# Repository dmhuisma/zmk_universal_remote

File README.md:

# ZMK Universal Remote

A simple remote for a living-room HTPC. Off-the-shelf remotes tend to feel cheap and lack the simple navigation people now expect from a streaming box. This remote has only the basic buttons a streaming box remote has: a D-pad, back, home and media controls. A touchscreen adds Home Assistant controls and a touchpad.

This repository contains the PCB, the 3D-printable case and the [ZMK](https://zmk.dev/) firmware.

> **Note:** This remote needs a second revision to solve connectivity issues. The antenna is placed under where you grip with your hand, which blocks the signal. The rev 2 design is currently in progress, so different parts of the design (board, firmware, case) may not match up in current state.

## Features

- **Streaming-box button layout:** a 5-way D-pad plus six buttons for navigation and media. There are no rows of rarely used buttons.
- **Quiet, soft-feeling buttons:** the remote uses Alps **SKPMAME010** tactile switches, which give soft tactile feedback instead of the loud clicks of cheaper remotes.
- **Touchscreen:** a 1.9" 170×320 capacitive touch LCD (Waveshare, ST7789V2 / CST816S) with a tabbed UI built with LVGL.
- **Home Assistant control over BTHome:** touchscreen buttons send BTHome Bluetooth advertisements, which nearby ESPHome Bluetooth proxies pick up. Taps and long presses are separate events.
- **Touchpad and air mouse:** the Touchpad screen controls the PC's mouse pointer. On that screen, tilting the remote also moves the pointer, using the accelerometer.
- **USB dongle connection:** a USB dongle plugged into the PC connects to the remote quickly and easily. *(Planned; not set up yet.)*
- **Infrared TX and RX:** two IR LEDs (wide and narrow beam) control TVs and other devices that aren't part of the smart home. A TSOP38238 receiver can learn codes from existing remotes.
- **Wake on motion:** an MPU6050 accelerometer wakes the remote from deep sleep when you pick it up, so you don't need to press a button first.
- **Display backlight:** adjustable brightness, and the backlight turns off when the remote is idle.
- **Rechargeable battery:** the case has room for a flat LiPo of about 1000 mAh (not verified yet). It charges over USB-C.
- **Sleep current:** 100 uA, with accelerometer motion wake enabled.
- **Active current:** >= 20 mA, depending on screen brightness
- **nice!nano (nRF52840) controller:** standard ZMK hardware with Bluetooth LE.

> **Note:** The touchscreen UI and its Home Assistant controls (scenes, lights, climate, vacuums) are built for my own home. If you build this remote, expect to customize the screens and automations for your setup. The physical buttons are general-purpose.

## Touchscreen interface

| Home: scenes | TV | TV › Mouse: touchpad |
|:---:|:---:|:---:|
|  |  |  |

## Repository layout

| Path | Contents |
|---|---|
| [`board/`](board/) | KiCad schematic and PCB |
| [`case/`](case/) | 3D-printable case (SolidCraft model and 3MF exports) |
| [`firmware/`](firmware/) | ZMK shield, custom drivers and Home Assistant tooling |

## Hardware

The PCB is a KiCad project. Main parts:

- nice!nano (nRF52840)
- 11 × Alps SKPMAME010 tactile switches in a diode matrix
- Waveshare 1.9" touch LCD (on a header)
- GY-521 MPU6050 accelerometer module (on a header)
- 2 × 5 mm IR LEDs driven by Si2302 MOSFETs, and a TSOP38238 IR receiver
- Flat LiPo battery, soldered directly to the nice!nano battery pads

> **Important:** Before you fit the GY-521 accelerometer module, desolder its power LED and its I2C pull-up resistors. The module stays powered during sleep, and with these parts left on, the sleep current is too high.

## Case

The case is modeled in SolidCraft ([`case/universal_remote_case.sc`](case/universal_remote_case.sc)). It is a two-part snap-fit shell with separate printed button caps, D-pad segments and an IR-transparent front window.

## Firmware

The firmware is a ZMK shield (`universal_remote`) for the `nice_nano//zmk` board. It also uses these modules:

- [zephyr-dt-lvgl](https://github.com/dmhuisma/zephyr-dt-lvgl): touchscreen UI defined in devicetree
- [zmk-ir](https://github.com/tadakado/zmk-ir): IR transmit and receive

The custom code in `firmware/src/` covers BTHome broadcasts, the touchpad, the motion pointer, wake-on-motion sleep and display brightness.

Build targets are listed in [`firmware/build.yaml`](firmware/build.yaml). This includes the `universal_remote_dongle` shield for an nRF52840 USB dongle. The local build and flash commands are in [`firmware/.vscode/tasks.json`](firmware/.vscode/tasks.json).

### Home Assistant

[`firmware/home_assistant/bthome_buttons.yaml`](firmware/home_assistant/bthome_buttons.yaml) lists every button the remote sends and the BTHome event each one fires. To generate a starter automation to edit:

```sh
cd firmware
uv run tools/gen_hass_automation.py home_assistant/bthome_buttons.yaml --address XX:XX:XX:XX:XX:XX
```

To watch the remote's advertisements live while you debug, use `tools/bthome_monitor.py`.

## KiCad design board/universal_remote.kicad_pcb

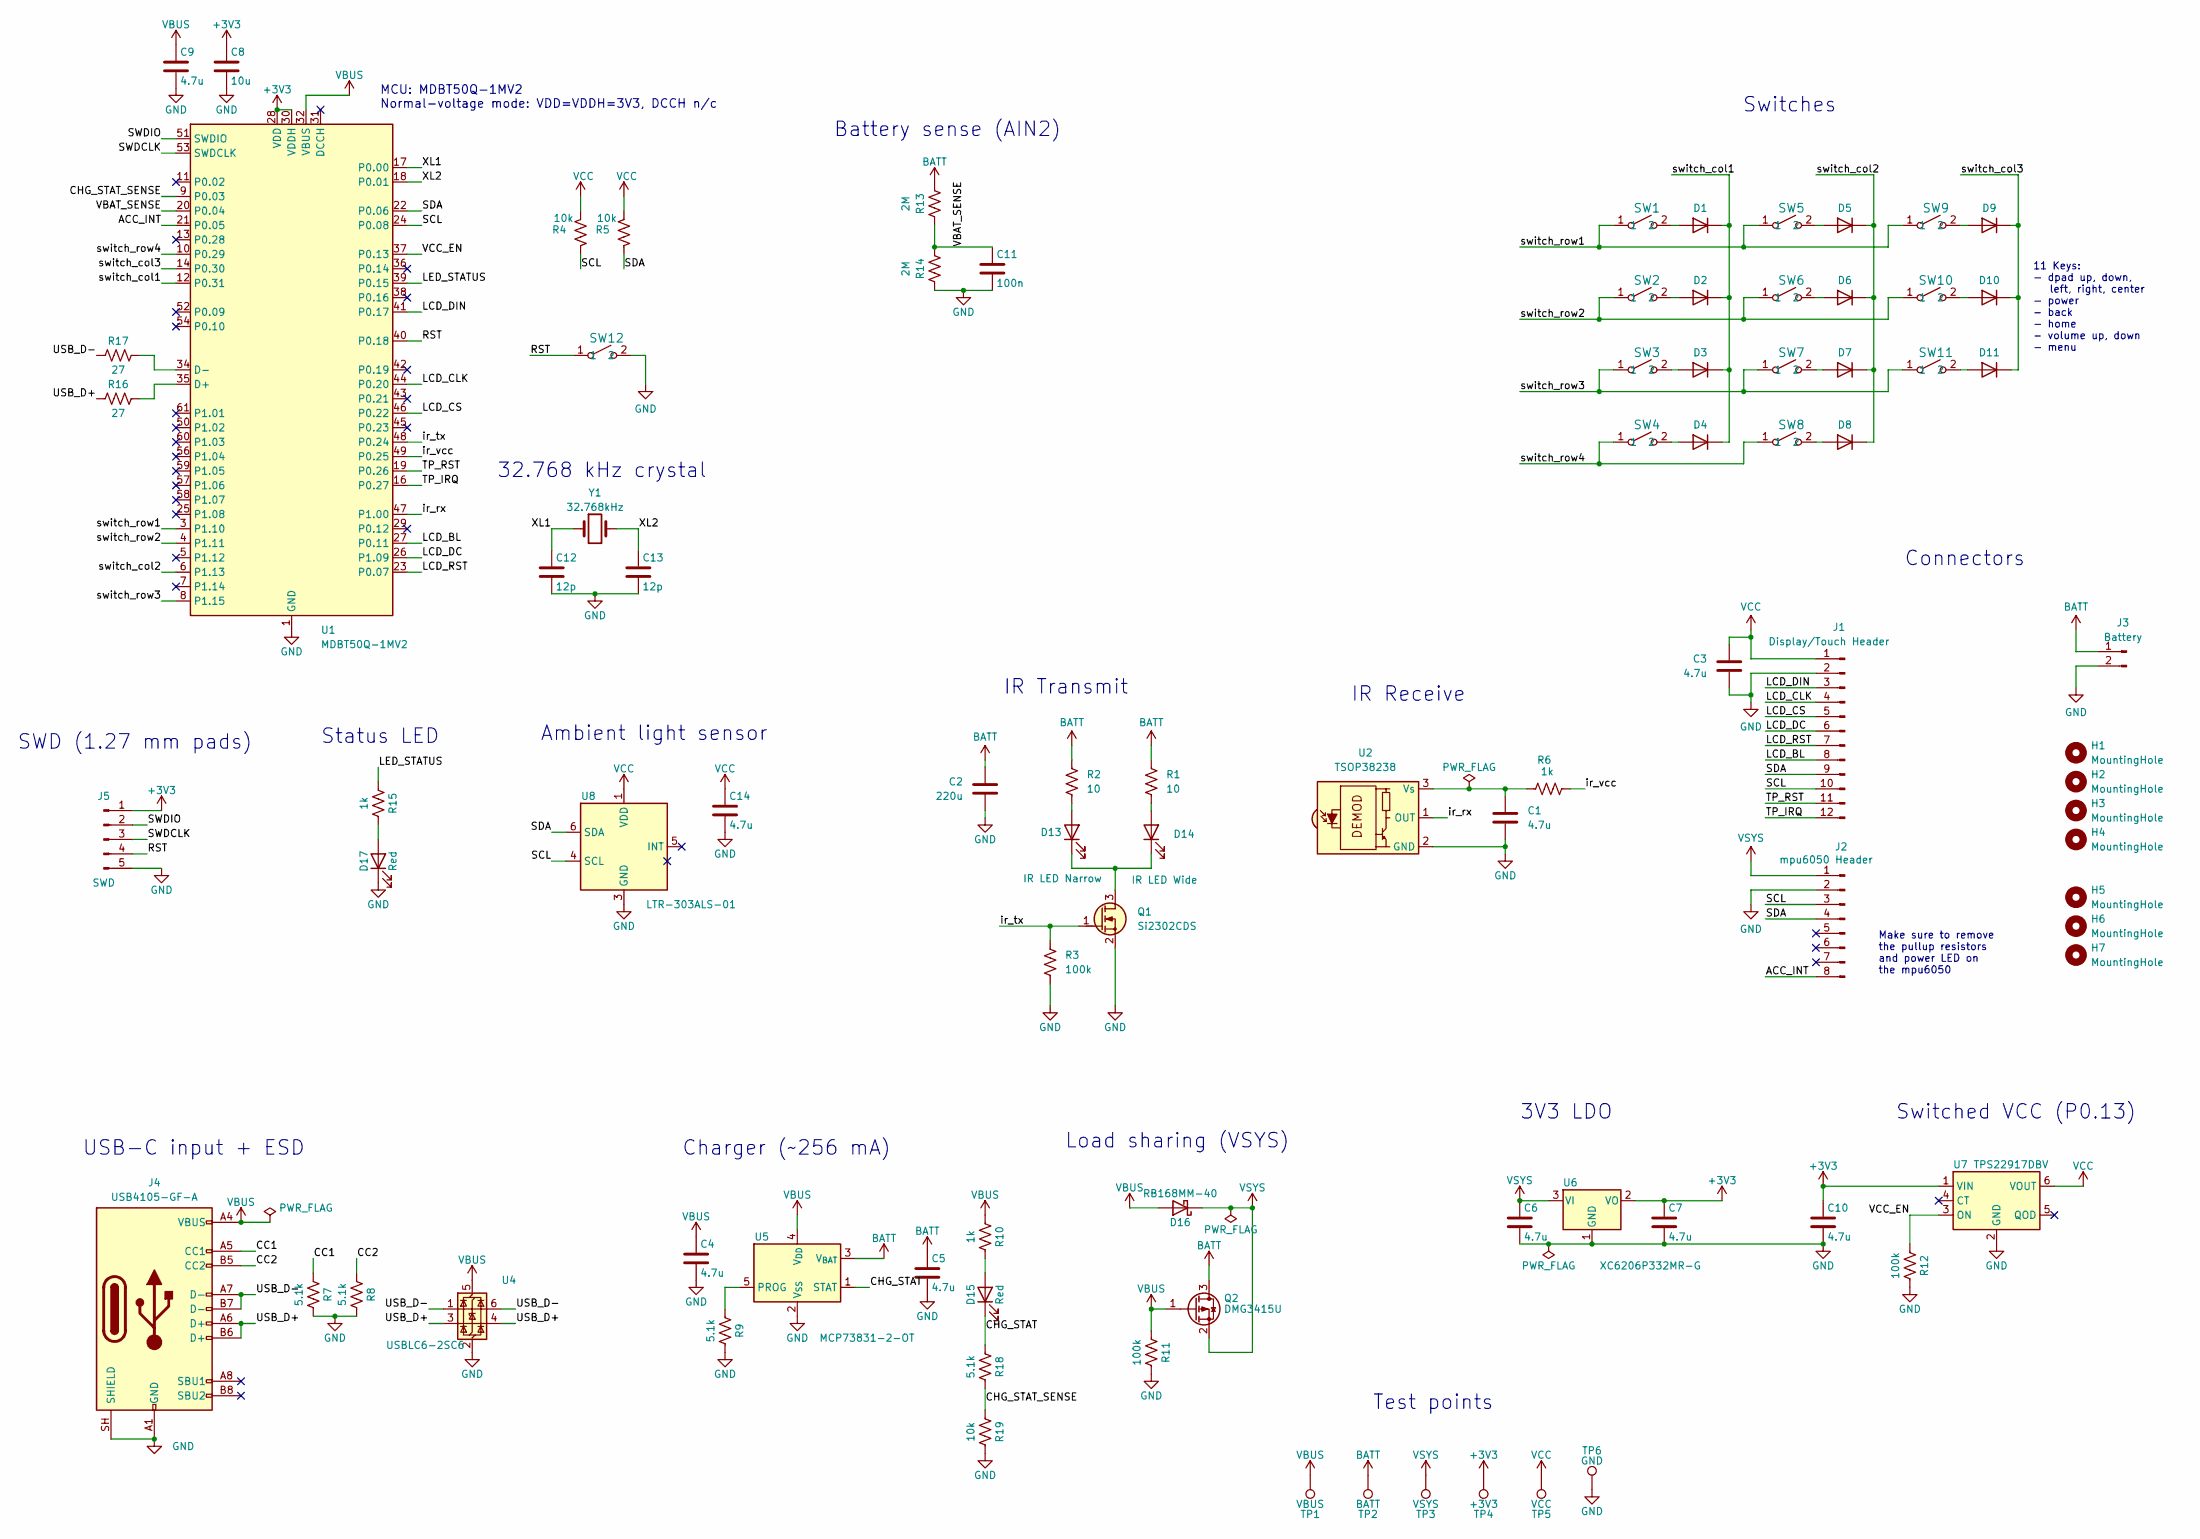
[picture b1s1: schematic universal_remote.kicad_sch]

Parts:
C1, C3, C4, C5, C6, C7, C9, C10, C14: 4.7u; C_0603_1608Metric_Pad1.08x0.95mm_HandSolder
C2: 220u; C_1210_3225Metric_Pad1.33x2.70mm_HandSolder
C8: 10u; C_0805_2012Metric_Pad1.18x1.45mm_HandSolder
C11: 100n; C_0603_1608Metric_Pad1.08x0.95mm_HandSolder
C12, C13: 12p; C_0603_1608Metric_Pad1.08x0.95mm_HandSolder
D1, D2, D3, D4, D5, D6, D7, D8, D9, D10, D11: D; D_DO-35_SOD27_P10.16mm_Horizontal
D13: IR LED Narrow; LED_D3.0mm; MPN Inolux INL-3AHIR15 (alt: INL-3AHIR30)
D14: IR LED Wide; LED_D3.0mm; MPN Everlight IR204/H16/L10 (DigiKey 1080-1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
D15, D17: Red; LED_0603_1608Metric_Pad1.05x0.95mm_HandSolder
D16: RB168MM-40; D_SOD-123F; MPN Rohm RB168MM-40TR (ultra-low IR, <=0.55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
H1, H2, H3, H4: MountingHole; MountingHole_2.2mm_M2
H5, H6, H7: MountingHole; MountingHole_3.2mm_M3
J1: Display/Touch Header; PinHeader_1x12_P2.54mm_Vertical
J2: mpu6050 Header; PinHeader_1x08_P2.54mm_Vertical
J3: Battery; PinHeader_1x02_P2.54mm_Vertical
J4: USB4105-GF-A; USB_C_Receptacle_GCT_USB4105-xx-A_16P_TopMnt_Horizontal; MPN GCT USB4105-GF-A
J5: SWD; PinHeader_1x05_P2.54mm_Vertical
Q1: Si2302CDS; SOT-23
Q2: DMG3415U; SOT-23; MPN DMG3415U-7
R1, R2: 10; R_1206_3216Metric_Pad1.30x1.75mm_HandSolder
R3, R11, R12: 100k; R_0603_1608Metric_Pad0.98x0.95mm_HandSolder
R4, R5, R19: 10k; R_0603_1608Metric_Pad0.98x0.95mm_HandSolder
R6, R10, R15: 1k; R_0603_1608Metric_Pad0.98x0.95mm_HandSolder
R7, R8, R9, R18: 5.1k; R_0603_1608Metric_Pad0.98x0.95mm_HandSolder
R13, R14: 2M; R_0603_1608Metric_Pad0.98x0.95mm_HandSolder
R16, R17: 27; R_0603_1608Metric_Pad0.98x0.95mm_HandSolder
SW1, SW2, SW3, SW4, SW5, SW6, SW7, SW8, SW9, SW10, SW11, SW12: SKPMAME010; SKPMAME010_ALPS
TP1: VBUS; TestPoint_Pad_D1.5mm
TP2: BATT; TestPoint_Pad_D1.5mm
TP3: VSYS; TestPoint_Pad_D1.5mm
TP4: +3V3; TestPoint_Pad_D1.5mm
TP5: VCC; TestPoint_Pad_D1.5mm
TP6: GND; TestPoint_Pad_D1.5mm
U1: MDBT50Q-1MV2; Raytac_MDBT50Q
U2: TSOP38238; Vishay_MINICAST-3Pin
U4: USBLC6-2SC6; SOT-23-6
U5: MCP73831-2-OT; SOT-23-5; MPN MCP73831T-2ACI/OT
U6: XC6206P332MR-G; SOT-23; MPN Torex XC6206P332MR-G (not the UMW XC620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
U7: TPS22917DBV; SOT-23-6
U8: LTR-303ALS-01; Lite-On_LTR-303ALS-01; MPN Lite-On LTR-303ALS-01
Y1: 32.768kHz; Crystal_SMD_3215-2Pin_3.2x1.5mm; MPN Abracon ABS07-32.768KHZ-9-T (CL 9 pF, E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

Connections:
+3V3: C7.1, C8.1, C10.1, J5.1, TP4.1 (1_1), U1.28 (VDD), U1.30 (VDDH), U6.2 (VO), U7.1 (VIN)
/ACC_INT: J2.8, U1.21 (P0.05)
/CC1: J4.A5 (CC1), R7.1
/CC2: J4.B5 (CC2), R8.1
/CHG_STAT: D15.1 (K), R18.1, U5.1 (STAT)
/CHG_STAT_SENSE: R18.2, R19.1, U1.9 (P0.03)
/LCD_BL: J1.8, U1.27 (P0.11)
/LCD_CLK: J1.4, U1.44 (P0.20)
/LCD_CS: J1.5, U1.46 (P0.22)
/LCD_DC: J1.6, U1.26 (P1.09)
/LCD_DIN: J1.3, U1.41 (P0.17)
/LCD_RST: J1.7, U1.23 (P0.07)
/LED_STATUS: R15.1, U1.39 (P0.15)
/RST: J5.4, SW12.1, U1.40 (P0.18)
/SCL: J1.10, J2.3, R4.2, U1.24 (P0.08), U8.4 (SCL)
/SDA: J1.9, J2.4, R5.2, U1.22 (P0.06), U8.6 (SDA)
/SWDCLK: J5.3, U1.53 (SWDCLK)
/SWDIO: J5.2, U1.51 (SWDIO)
/TP_IRQ: J1.12, U1.16 (P0.27)
/TP_RST: J1.11, U1.19 (P0.26)
/USB_D+: J4.A6 (D+), J4.B6 (D+), R16.1, U4.3 (I/O2), U4.4 (I/O2)
/USB_D-: J4.A7 (D-), J4.B7 (D-), R17.1, U4.1 (I/O1), U4.6 (I/O1)
/VBAT_SENSE: C11.1, R13.2, R14.1, U1.20 (P0.04)
/VCC_EN: R12.1, U1.37 (P0.13), U7.3 (ON)
/XL1: C12.1, U1.17 (P0.00), Y1.1
/XL2: C13.1, U1.18 (P0.01), Y1.2
/ir_rx: U1.47 (P1.00), U2.1 (OUT)
/ir_tx: Q1.1 (G), R3.2, U1.48 (P0.24)
/ir_vcc: R6.2, U1.49 (P0.25)
/switch_col1: D1.1 (K), D2.1 (K), D3.1 (K), D4.1 (K), U1.12 (P0.31)
/switch_col2: D5.1 (K), D6.1 (K), D7.1 (K), D8.1 (K), U1.6 (P1.13)
/switch_col3: D9.1 (K), D10.1 (K), D11.1 (K), U1.14 (P0.30)
/switch_row1: SW1.1, SW5.1, SW9.1, U1.3 (P1.10)
/switch_row2: SW2.1, SW6.1, SW10.1, U1.4 (P1.11)
/switch_row3: SW3.1, SW7.1, SW11.1, U1.8 (P1.15)
/switch_row4: SW4.1, SW8.1, U1.10 (P0.29)
BATT: C2.2, C5.1, J3.1, Q2.3 (D), R1.1, R2.1, R13.1, TP2.1 (1_1), U5.3 (V_{BAT})
unnamed: D1.2 (A), SW1.2
unnamed: D2.2 (A), SW2.2
unnamed: D3.2 (A), SW3.2
unnamed: D4.2 (A), SW4.2
unnamed: D5.2 (A), SW5.2
unnamed: D6.2 (A), SW6.2
unnamed: D7.2 (A), SW7.2
unnamed: D8.2 (A), SW8.2
unnamed: D9.2 (A), SW9.2
unnamed: D10.2 (A), SW10.2
unnamed: D11.2 (A), SW11.2
unnamed: D13.2 (A), R2.2
unnamed: D13.1 (K), D14.1 (K), Q1.3 (D)
unnamed: D14.2 (A), R1.2
unnamed: D15.2 (A), R10.2
unnamed: D17.2 (A), R15.2
unnamed: R16.2, U1.35 (D+)
unnamed: R17.2, U1.34 (D-)
unnamed: R9.1, U5.5 (PROG)
VCC: C3.2, C14.1, J1.1, R4.1, R5.1, TP5.1 (1_1), U7.6 (VOUT), U8.1 (VDD)

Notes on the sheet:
Ambient light sensor
SWD (1.27 mm pads)
Switches
USB-C input + ESD
IR Receive
Connectors
Battery sense (AIN2)
3V3 LDO
Charger (~256 mA)
Make sure to remove the pullup resistors and power LED on the mpu6050
MCU: MDBT50Q-1MV2 Normal-voltage mode: VDD=VDDH=3V3, DCCH n/c
Test points
Switched VCC (P0.13)
11 Keys: - dpad up, down, left, right, center - power - back - home - volume up, down - menu
Status LED
IR Transmit
Load sharing (VSYS)
32.768 kHz crystal

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
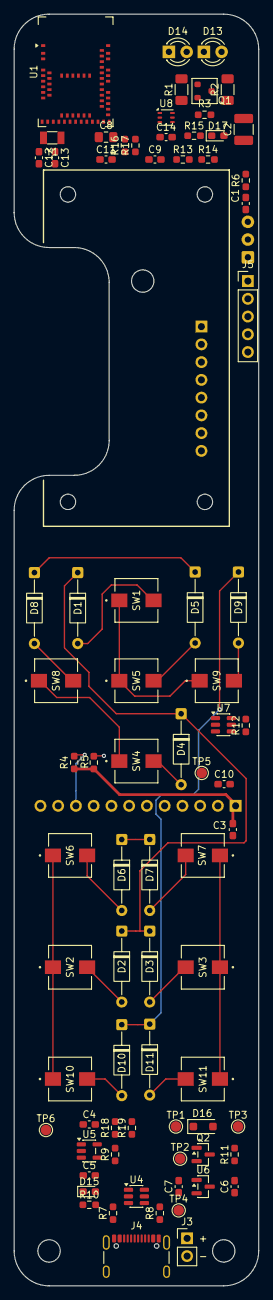
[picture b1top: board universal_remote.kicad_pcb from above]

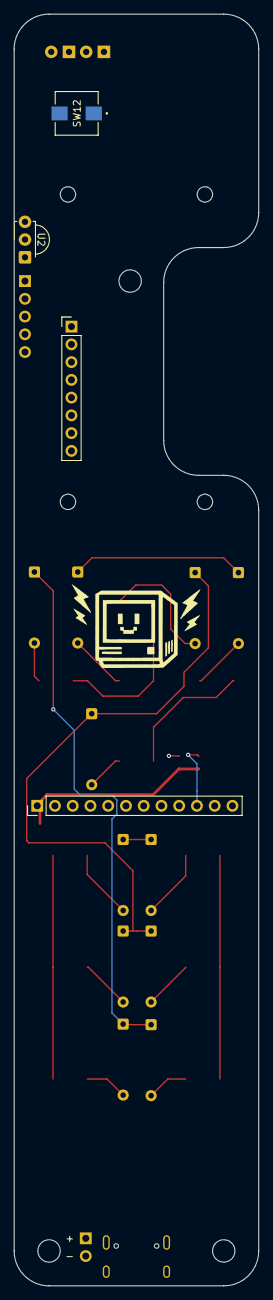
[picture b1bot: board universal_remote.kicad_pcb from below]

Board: 2 copper layers, 35.0 x 182.0 mm, 89 parts (4 on the bottom side), 61 nets.
